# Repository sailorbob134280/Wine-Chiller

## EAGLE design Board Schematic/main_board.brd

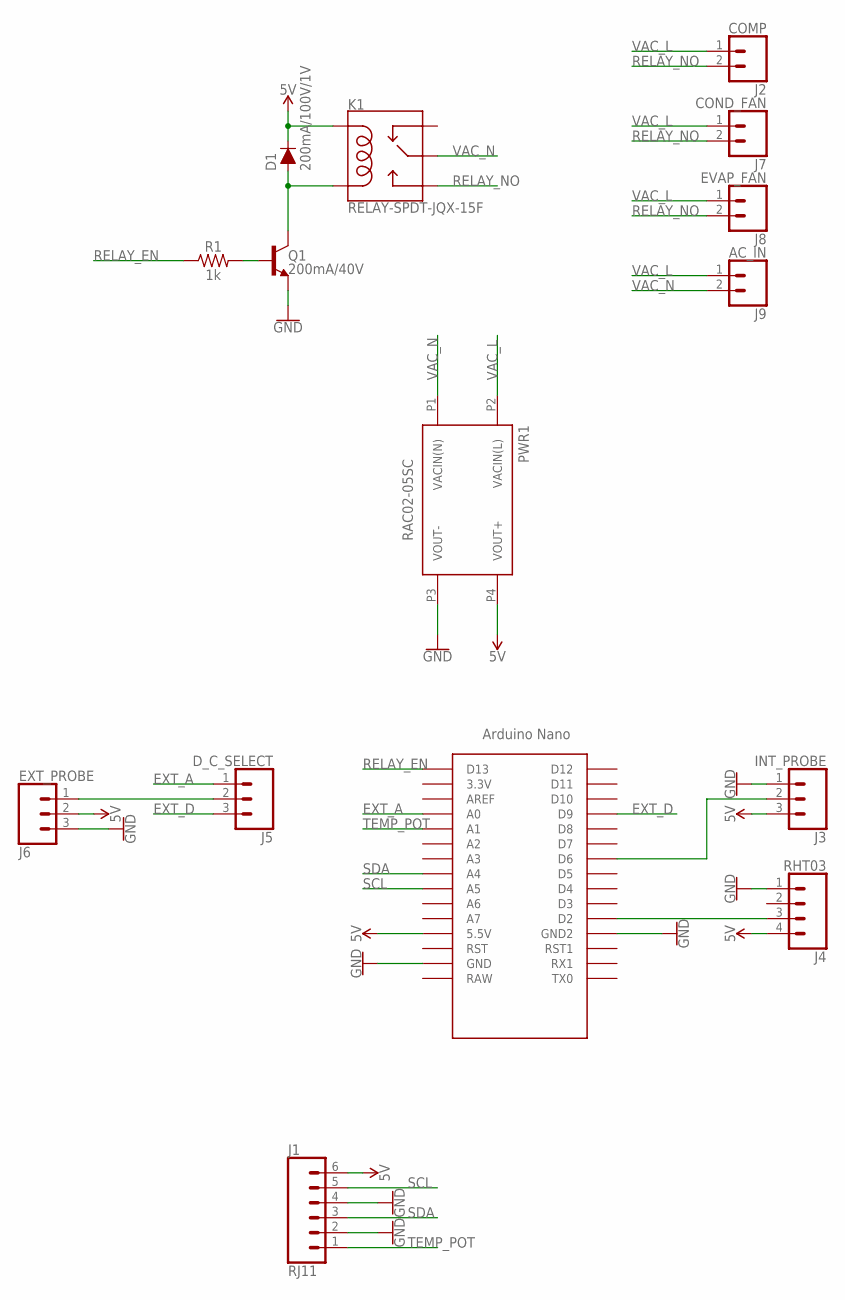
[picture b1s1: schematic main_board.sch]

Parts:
D1: 200mA/100V/1V; DIODE-1N4148
J1: RJ11; RJ11-6
J2: COMP; SCREWTERMINAL-5MM-2
J3: INT_PROBE; 1X03
J4: RHT03; 1X04
J5: D_C_SELECT; 1X03
J6: EXT_PROBE; 1X03
J7: COND_FAN; SCREWTERMINAL-5MM-2
J8: EVAP_FAN; SCREWTERMINAL-5MM-2
J9: AC_IN; SCREWTERMINAL-5MM-2
K1: RELAY-SPDT-JQX-15F; RELAY-T90
PWR1: RAC02-05SC; LOW_PROFILE_POWER_MODULE
Q1: 200mA/40V; TO-92
R1: 1k; AXIAL-0.3
U$1: NANO

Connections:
5V: D1.C, J1.6, J3.3, J4.4, J6.2, K1.COIL1, PWR1.P4 (VOUT+), U$1.5V (5.5V)
EXT_A: J5.1, U$1.A0
EXT_D: J5.3, U$1.D9
GND: J1.2, J1.4, J3.1, J4.1, J6.3, PWR1.P3 (VOUT-), Q1.1 (E), U$1.GND, U$1.GND1 (GND2)
unnamed: Q1.2 (B), R1.P$2 (2)
unnamed: D1.A, K1.COIL2, Q1.3 (C)
unnamed: J4.3, U$1.D2
unnamed: J3.2, U$1.D6
unnamed: J5.2, J6.1
RELAY_EN: R1.P$1 (1), U$1.D13
RELAY_NO: J2.2, J7.2, J8.2, K1.NO
SCL: J1.5, U$1.A5
SDA: J1.3, U$1.A4
TEMP_POT: J1.1, U$1.A1
VAC_L: J2.1, J7.1, J8.1, J9.1, PWR1.P2 (VACIN(L))
VAC_N: J9.2, K1.MAIN, PWR1.P1 (VACIN(N))

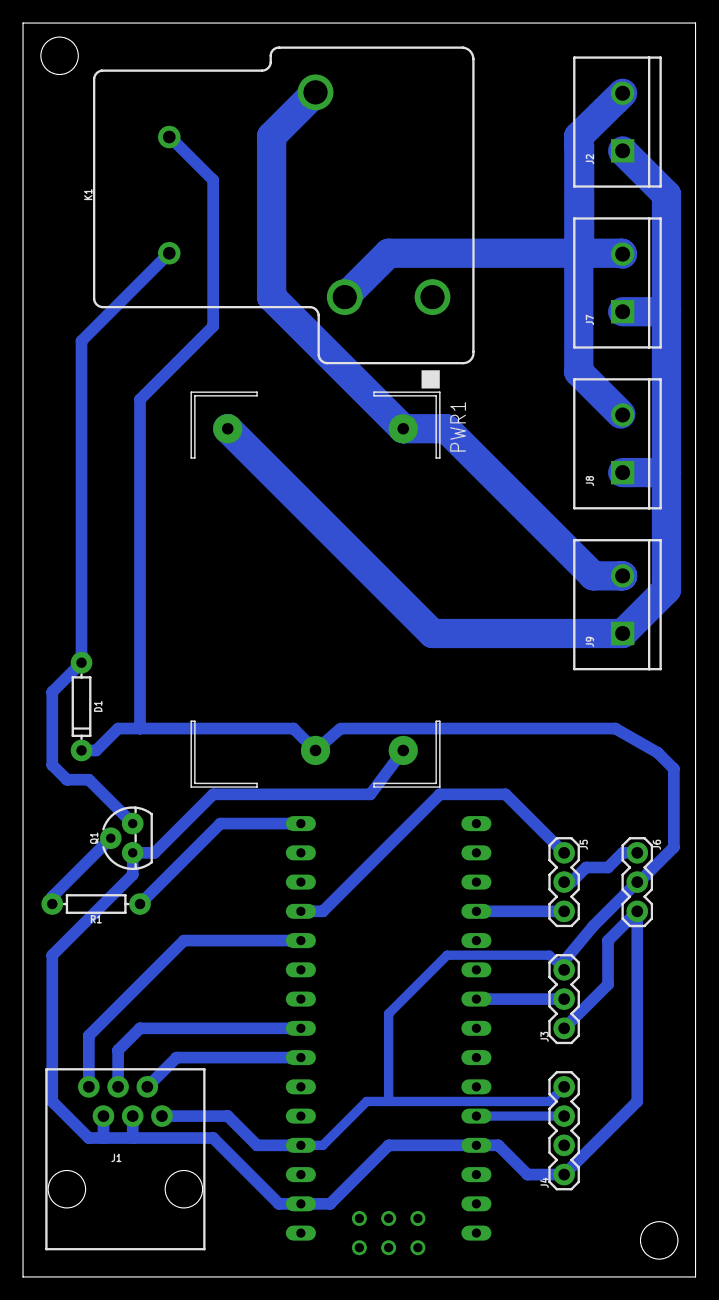
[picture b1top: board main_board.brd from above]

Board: 2 copper layers, 58.4 x 108.9 mm, 16 parts (0 on the bottom side), 16 nets.

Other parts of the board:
DRILEGEND: DRILEGEND

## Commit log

2019-03-05 Created repo
2019-03-05 display working
2019-03-05 Display now cycles appropriately, as well as displaying set temp
2019-03-06 Code working, ready for test. Note: pins not assigned correctly yet
2019-03-06 Added board schematic and CAD files
2019-03-06 Fixed a trace clearance issue
2019-03-10 code working, need to add other probes
2019-09-08 Cleanup and BOM addition

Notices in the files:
parts and their libraries:
SparkFun-DiscreteSemi: Licensing: Creative Commons ShareAlike 4.0 International - https://creativecommons.org/licenses/by-sa/4.0
